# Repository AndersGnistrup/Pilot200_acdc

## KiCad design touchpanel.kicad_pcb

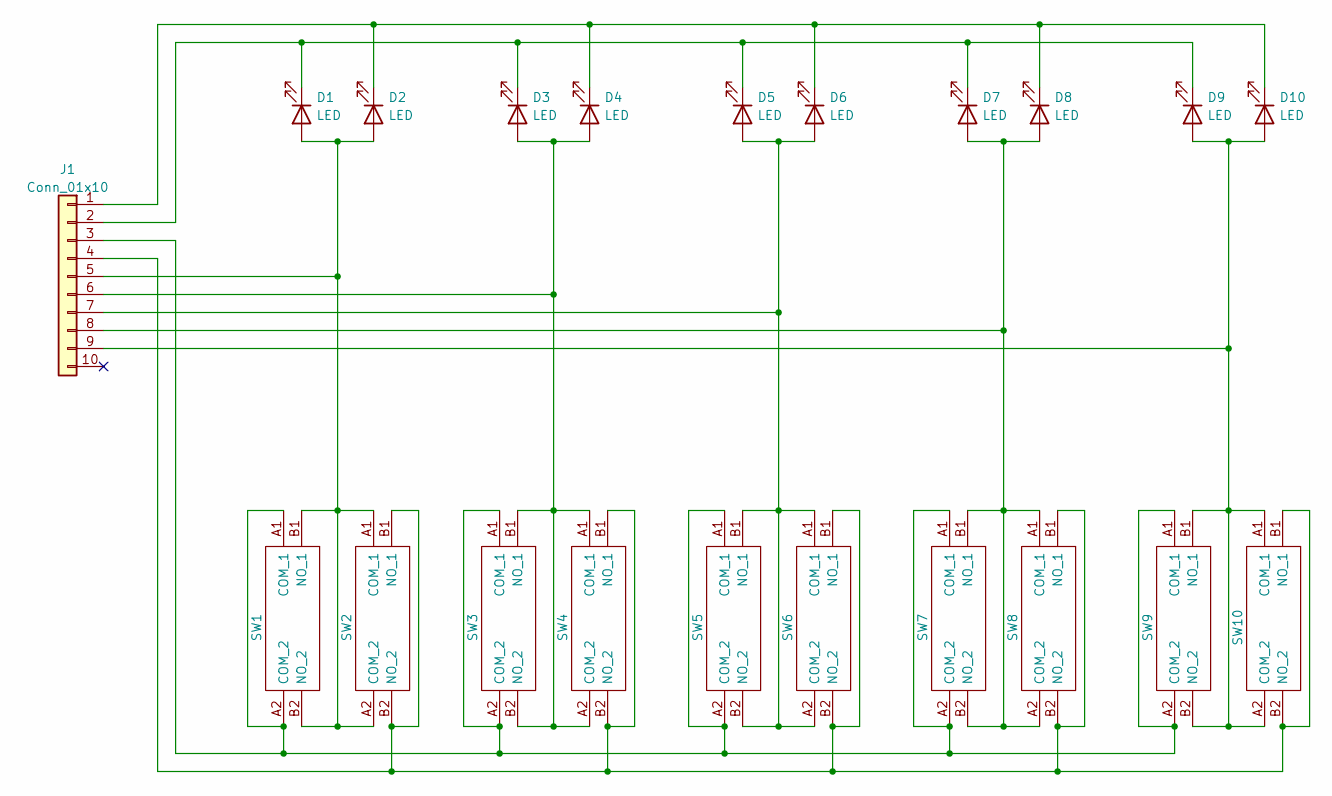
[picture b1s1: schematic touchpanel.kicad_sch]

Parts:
D1, D2, D3, D4, D5, D6, D7, D8, D9, D10: LED; LEDM3528X210N
J1: Conn_01x10; PinHeader_1x10_P2.54mm_Vertical
SW1, SW2, SW3, SW4, SW5, SW6, SW7, SW8, SW9, SW10: SW_Push; EVQQ2201W; Manufacturer_Part_Number EVQ-Q2201W; Mouser Part Number 667-EVQ-Q2201W

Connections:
unnamed: D1.1 (K), D3.1 (K), D5.1 (K), D7.1 (K), D9.1 (K), J1.2
unnamed: D1.2 (A), D2.2 (A), J1.5, SW1.B1 (NO_1), SW1.B2 (NO_2), SW2.A1 (COM_1), SW2.A2 (COM_2)
unnamed: D3.2 (A), D4.2 (A), J1.6, SW3.B1 (NO_1), SW3.B2 (NO_2), SW4.A1 (COM_1), SW4.A2 (COM_2)
unnamed: D5.2 (A), D6.2 (A), J1.7, SW5.B1 (NO_1), SW5.B2 (NO_2), SW6.A1 (COM_1), SW6.A2 (COM_2)
unnamed: D7.2 (A), D8.2 (A), J1.8, SW7.B1 (NO_1), SW7.B2 (NO_2), SW8.A1 (COM_1), SW8.A2 (COM_2)
unnamed: D2.1 (K), D4.1 (K), D6.1 (K), D8.1 (K), D10.1 (K), J1.1
unnamed: D9.2 (A), D10.2 (A), J1.9, SW9.B1 (NO_1), SW9.B2 (NO_2), SW10.A1 (COM_1), SW10.A2 (COM_2)
unnamed: J1.3, SW1.A1 (COM_1), SW1.A2 (COM_2), SW3.A1 (COM_1), SW3.A2 (COM_2), SW5.A1 (COM_1), SW5.A2 (COM_2), SW7.A1 (COM_1), SW7.A2 (COM_2), SW9.A1 (COM_1), SW9.A2 (COM_2)
unnamed: J1.4, SW2.B1 (NO_1), SW2.B2 (NO_2), SW4.B1 (NO_1), SW4.B2 (NO_2), SW6.B1 (NO_1), SW6.B2 (NO_2), SW8.B1 (NO_1), SW8.B2 (NO_2), SW10.B1 (NO_1), SW10.B2 (NO_2)

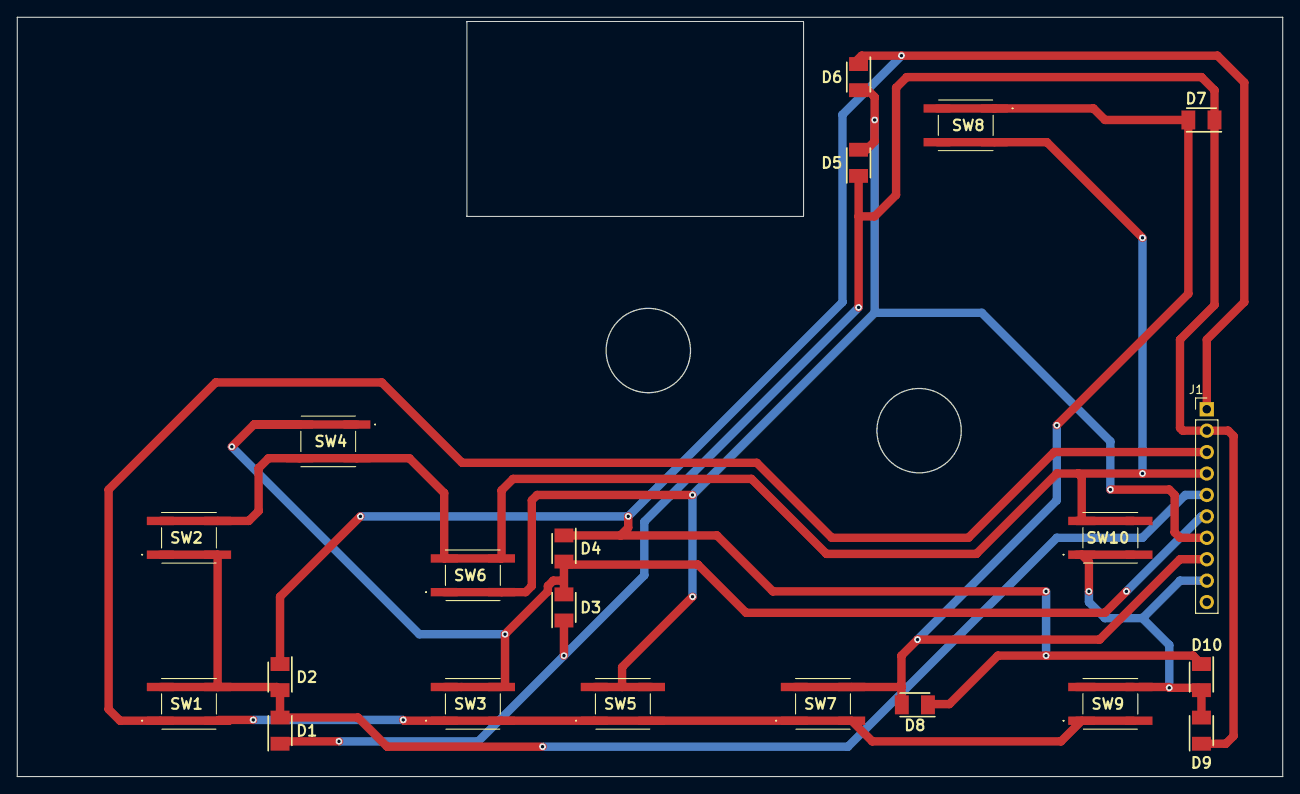
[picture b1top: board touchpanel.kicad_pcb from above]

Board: 2 copper layers, 150.0 x 90.0 mm, 21 parts (0 on the bottom side), 9 nets.

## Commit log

2023-01-22 first version of the pilot200 AC/DC interface print
2023-02-02 Front of print added.
